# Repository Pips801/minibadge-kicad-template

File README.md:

# KiCad 7/8/9(?) Minibadge Template

## How to import and use template
* Open KiCad
* Go to **File -> New Project From Template**
* 
* Go to **User Templates**
* 
* Copy the default path to the Templates folder (your documents folder) and open it up
* Copy this folder into the templates folder
* 
* Close and Re-Open the KiCad New Project From Template window
* Go to **User Templates**
* You will see the SAINTCON Minibadge Template
* 
* Click **OK**
* Name your Minibadge project and select a location

Adapted from the Minibadge framework found here https://github.com/lukejenkins/minibadge

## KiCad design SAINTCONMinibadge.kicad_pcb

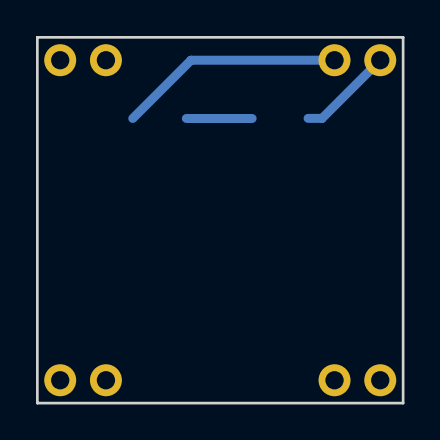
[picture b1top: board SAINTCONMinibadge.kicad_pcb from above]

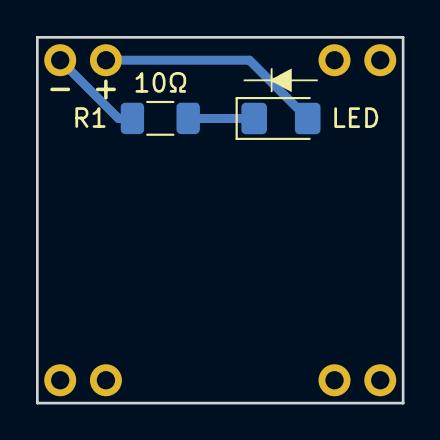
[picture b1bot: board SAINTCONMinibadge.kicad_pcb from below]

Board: 2 copper layers, 20.3 x 20.3 mm, 3 parts (2 on the bottom side), 3 nets.

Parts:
LED: LED; LED_1206_3216Metric_Pad1.42x1.75mm_HandSolder
R1: R; R_1206_3216Metric_Pad1.30x1.75mm_HandSolder
X1: SAINTCON-Minibadge-Simple

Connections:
unnamed: LED.2 (A), X1.7 (+3v3)
unnamed: LED.1 (K), R1.2
unnamed: R1.1, X1.8 (GND)

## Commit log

2025-07-23 Move from Minibadge project to seperate
